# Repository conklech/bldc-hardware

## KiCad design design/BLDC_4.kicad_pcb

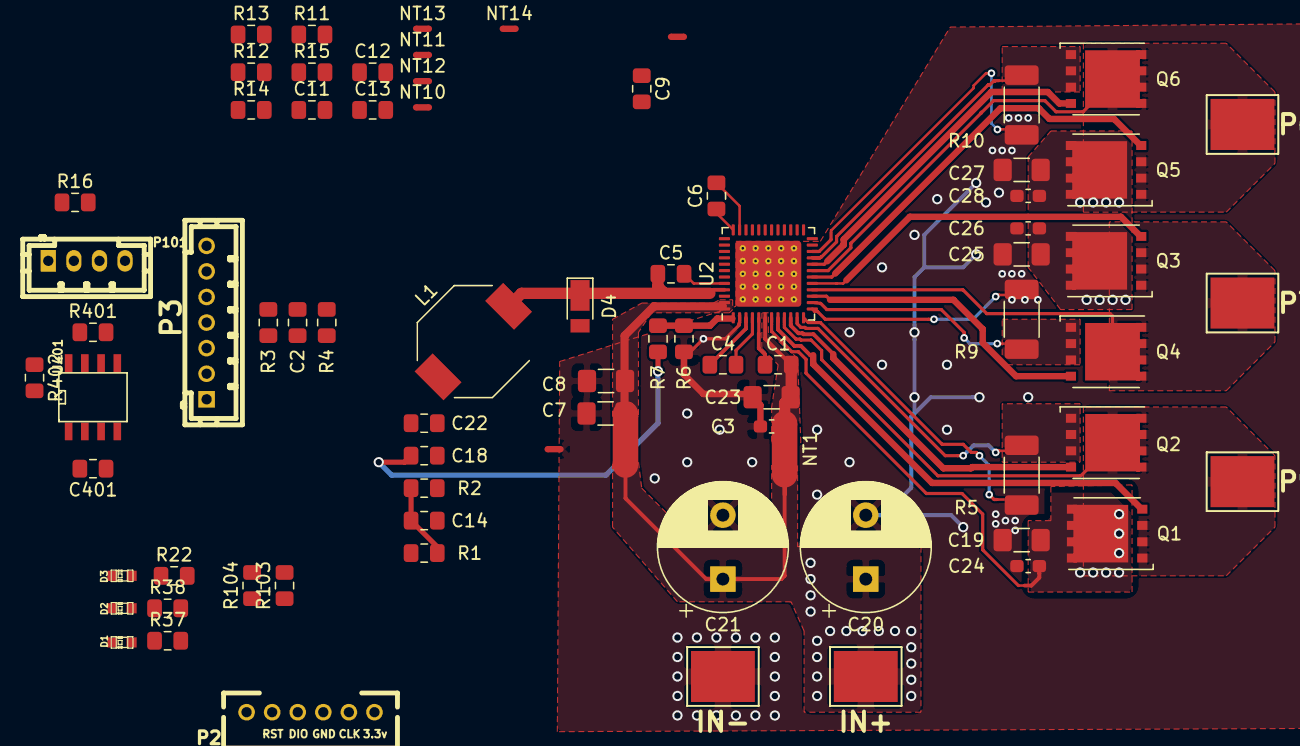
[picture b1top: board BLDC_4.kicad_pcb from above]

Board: 2 copper layers, 78 parts (0 on the bottom side), 49 nets.

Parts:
C1, C6, C9: 1u; C_0805_2012Metric_Pad1.15x1.40mm_HandSolder
C2, C5: 0.1u 16V; C_0805_2012Metric_Pad1.15x1.40mm_HandSolder
C3, C24, C26, C28: 0.1u 50V; C_0603_1608Metric_Pad1.05x0.95mm_HandSolder
C4: 47n 50V low-ESR; C_0805_2012Metric_Pad1.15x1.40mm_HandSolder
C7, C8, C19, C25, C27: 2.2u 50V; C_1206_3216Metric_Pad1.42x1.75mm_HandSolder
C11, C12, C13, C14, C401: 2.2u; C_0805_2012Metric_Pad1.15x1.40mm_HandSolder
C18, C22: 10u; C_0805_2012Metric_Pad1.15x1.40mm_HandSolder
C20, C21: 220u 50V; CP_Radial_D10.0mm_P5.00mm
C23: 10u 50V; C_1206_3216Metric_Pad1.42x1.75mm_HandSolder
D1: GREEN; LED-0603
D2: RED; LED-0603
D3: LED; LED-0603
D4: D_Schottky_Small_ALT; D_PowerDI-123
L1: 33uH, 100mOhm; L_Bourns-SRU8043
NT1, NT3: Net-Tie_2; NetTie-2_SMD_Pad2.0mm
NT2, NT5, NT10, NT11, NT12, NT13, NT14: Net-Tie_2; NetTie-2_SMD_Pad0.5mm
NT6: Net-Tie_8mil; NetTie-2_SMD_Pad-8mil
P2: SWD; MICRO_JST_6
P3: PWR_COMM; b7b-ph-kl
P4: IN+; 1PAD_4x5mm
P5: IN-; 1PAD_4x5mm
P6: MOTOR1; 1PAD_4x5mm
P7: MOTOR2; 1PAD_4x5mm
P9: MOTOR3; 1PAD_4x5mm
P101: CANBUS; b4b-ph-kl
Q1, Q2, Q3, Q4, Q5, Q6: CSD19531Q5A; TDSON-8-1
R1: NTC 10k; R_0805_2012Metric_Pad1.15x1.40mm_HandSolder
R2, R402: 10k; R_0805_2012Metric_Pad1.15x1.40mm_HandSolder
R3, R12, R14, R16: 39k; R_0805_2012Metric_Pad1.15x1.40mm_HandSolder
R4, R11, R13, R15, R22: 2k2; R_0805_2012Metric_Pad1.15x1.40mm_HandSolder
R5, R9, R10: R010 1%; R_2010_Shunt_HandSolder
R6: 8.45k; R_0805_2012Metric_Pad1.15x1.40mm_HandSolder
R7: 28k; R_0805_2012Metric_Pad1.15x1.40mm_HandSolder
R37, R38: 100R; R_0805_2012Metric_Pad1.15x1.40mm_HandSolder
R103, R104: 22R; R_0805_2012Metric_Pad1.15x1.40mm_HandSolder
R401: NI; R_0805_2012Metric_Pad1.15x1.40mm_HandSolder
U2: DRV8323RS; Texas_S-PVQFN-N48_EP5.15x5.15mm_ThermalVias
U401: SN65HVD232; SOIC-8-W

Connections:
+5V: P3.1, P101.4
/CAN bus transceiver/CANH: P101.3, R401.1, U401.7
/CAN bus transceiver/CANL: P101.2, R401.2, U401.6
/MCU/ADC_TEMP: C14.1, R1.2, R2.1
/MCU/AN_IN: C2.2, R3.2, R4.2
/MCU/H1_VS: P9.1, Q1.1, Q1.2, Q1.3, Q2.5, R12.1, U2.9
/MCU/H2_VS: P7.1, Q3.1, Q3.2, Q3.3, Q4.5, R14.1, U2.16
/MCU/H3_VS: P6.1, Q5.1, Q5.2, Q5.3, Q6.5, R16.1, U2.19
/Mosfet driver/M_H1: Q1.4, U2.8
/Mosfet driver/M_H2: Q3.4, U2.17
/Mosfet driver/M_H3: Q5.4, U2.18
/Mosfet driver/M_L1: Q2.4, U2.10
/Mosfet driver/M_L2: Q4.4, U2.15
/Mosfet driver/M_L3: Q6.4, U2.20
/Mosfet driver/SH1+: R5.2, U2.11
/Mosfet driver/SH1-: R5.3, U2.12
/Mosfet driver/SH2+: R9.3, U2.14
/Mosfet driver/SH2-: R9.2, U2.13
/Mosfet driver/SH3+: R10.2, U2.21
/Mosfet driver/SH3-: R10.3, U2.22
/Mosfet driver/SW: C5.1, D4.1, L1.1, U2.45
/Mosfet driver/VCP: C1.1, U2.5
/Mosfet driver/VDRAIN: NT6.1, U2.7
/Mosfet driver/VIN: C7.1, C8.1, NT3.1, U2.47, U2.48
/Mosfet driver/VM_PIN: C1.2, C3.1, C23.1, NT1.1, U2.6
/Power MOSFETS/L1_S: Q2.1, Q2.2, Q2.3, R5.1
/Power MOSFETS/L2_S: Q4.1, Q4.2, Q4.3, R9.4
/Power MOSFETS/L3_S: Q6.1, Q6.2, Q6.3, R10.1
GND: C2.1, C6.2, C11.1, C12.1, C13.1, C14.2, C18.1, C22.1, C401.1, D1.2, D2.2, D3.2, D4.2, NT2.1, NT5.1, P2.3, P3.3, P101.1, R2.2, R4.1, R11.1, R13.1, R15.1, R402.2, U2.35, U2.43, U401.2
GNDPWR: C3.2, C7.2, C8.2, C19.1, C20.2, C21.2, C23.2, C24.1, C25.1, C26.1, C27.1, C28.1, NT2.2, P5.1, R5.4, R6.2, R9.1, R10.4, U2.2, U2.49
unnamed: C4.1, U2.3
unnamed: C4.2, U2.4
unnamed: C5.2, U2.44
unnamed: C6.1, U2.36
unnamed: C9.1, NT5.2, U2.27
unnamed: C11.2, NT10.1
unnamed: C12.2, NT11.1
unnamed: C13.2, NT12.1
unnamed: C401.2, NT14.1, U401.3
unnamed: D1.1, R37.1
unnamed: D2.1, R38.1
unnamed: D3.1, R22.1
unnamed: R6.1, R7.2, U2.1
unnamed: R11.2, R12.2
unnamed: R13.2, R14.2
unnamed: R15.2, R16.2
unnamed: R402.1, U401.8
VCC: C9.2, C18.2, C22.2, L1.2, NT10.2, NT11.2, NT12.2, NT13.2, NT14.2, P2.1, P3.2, R1.1, R7.1, R22.2, U2.26
V_SUPPLY: C19.2, C20.1, C21.1, C24.2, C25.2, C26.2, C27.2, C28.2, NT1.2, NT3.2, NT6.2, P4.1, Q1.5, Q3.5, Q5.5, R3.1
